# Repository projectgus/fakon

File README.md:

# Fakon

Fakon is open source hardware and software to present a Fake Hyundai Kona (*groan*) to transplanted powertrain modules taken from a real Hyundai Kona.

For more information, see [this blog post](https://projectgus.com/2024/12/fakon/).

## Disclaimers

Fakon is in early stage development, pre-alpha quality. Electric Vehicle modification involves serious risks, and there are zero guarantees about Fakon's quality, safety, or suitability for any purpose.

Fakon is developed exclusively through black-box reverse engineering techniques, and as such is prone to errors made in the reverse engineering process.

No content in Fakon is a derived work of any Copyrighted material owned by the Hyundai Kia Motor Company (HKMC) or their OEM suppliers.

## Licenses

* Software is licensed under the Mozilla Public License 2.0
* Hardware is licensed under the TAPR Open Hardware License 1.0

See LICENSE files for more details.

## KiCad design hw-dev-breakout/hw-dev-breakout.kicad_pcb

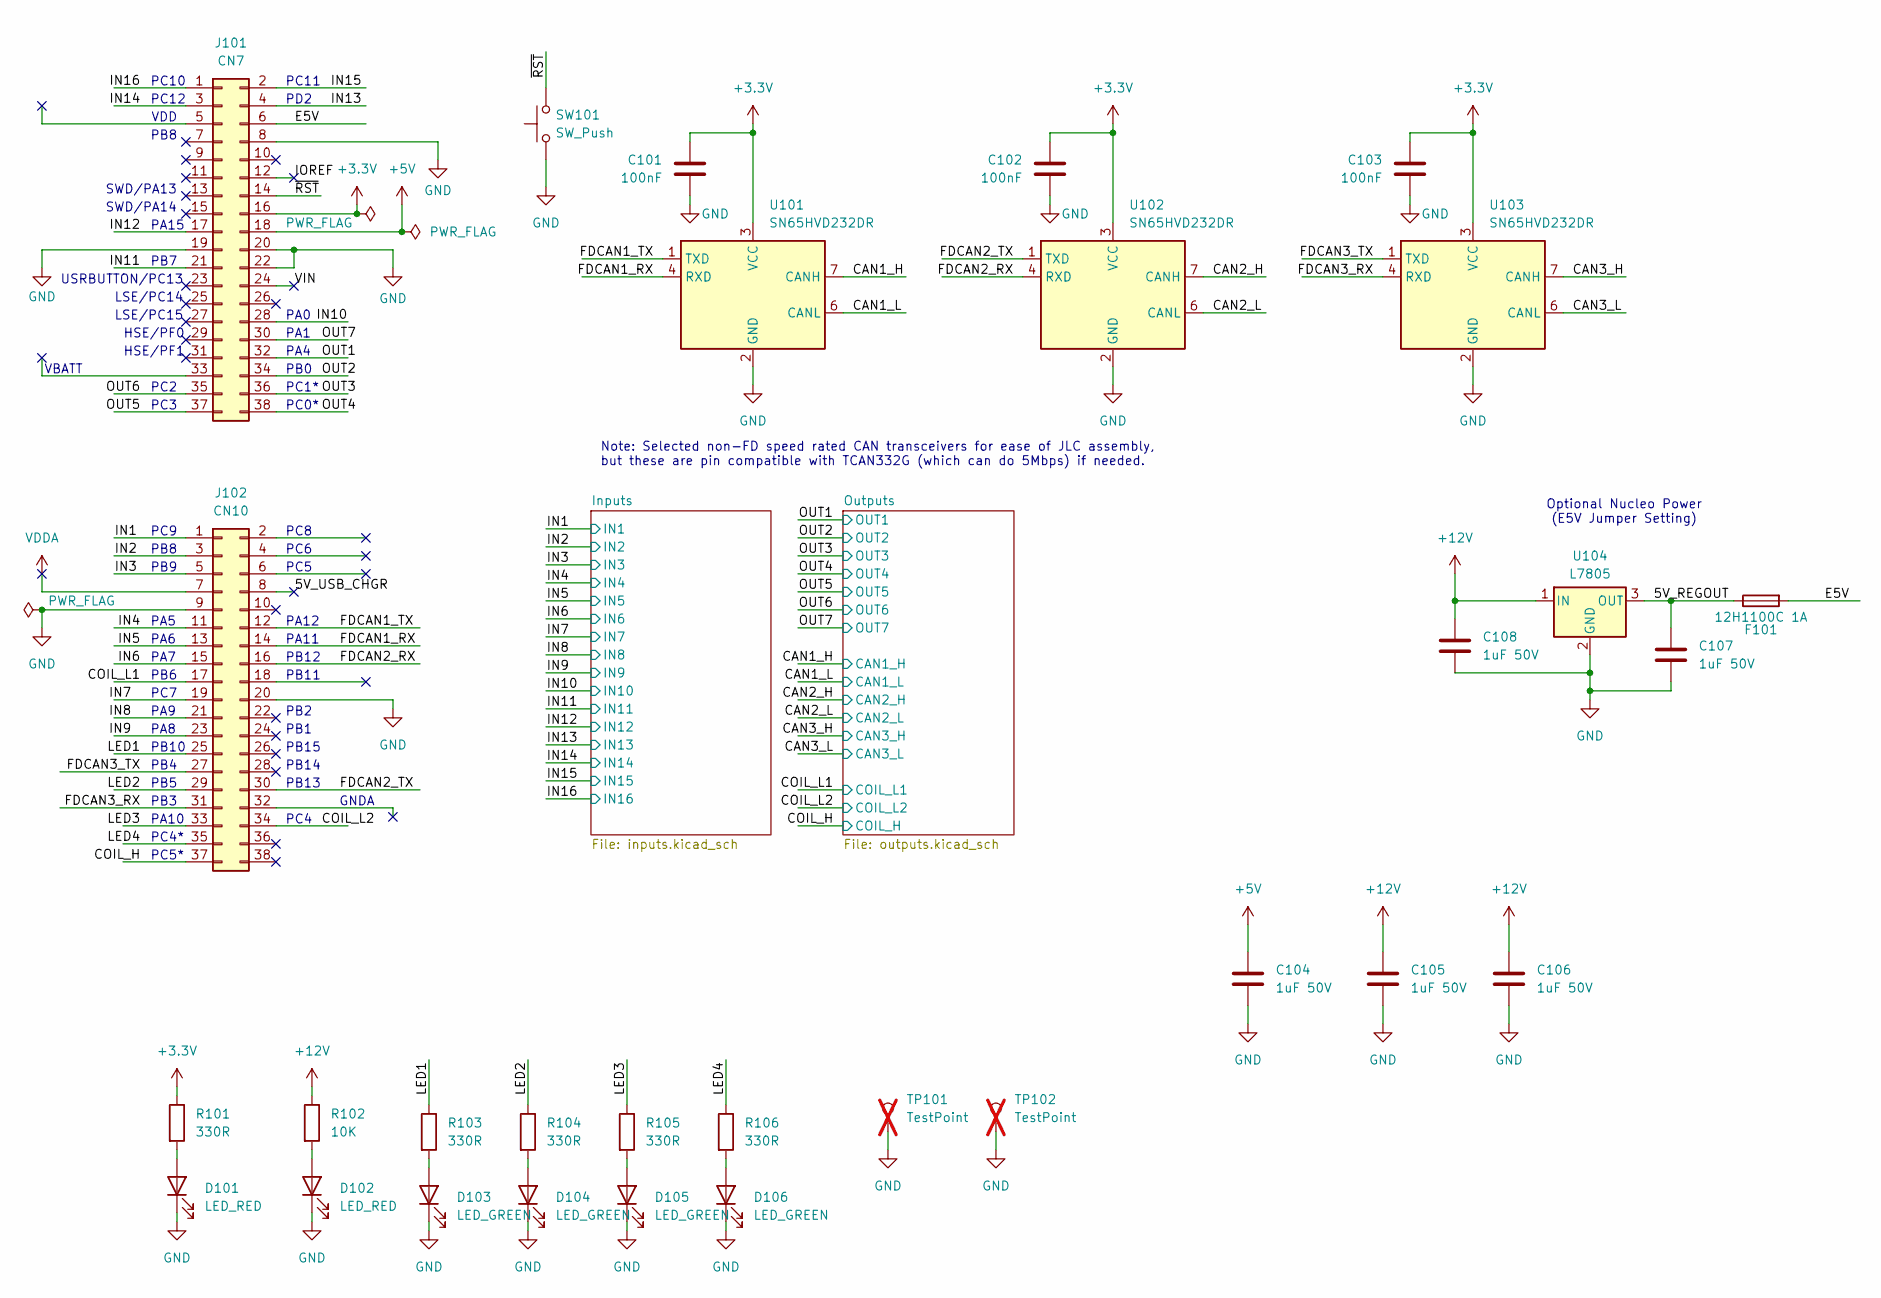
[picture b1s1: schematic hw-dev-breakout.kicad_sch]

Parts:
C101, C102, C103: 100nF; C_0603_1608Metric; LCSC Part # C14663
C104, C105, C106, C107, C108: 1uF 50V; C_1206_3216Metric; LCSC Part # C1848
D101, D102: LED_RED; LED_0603_1608Metric; LCSC Part # C2286
D103, D104, D105, D106: LED_GREEN; LED_0805_2012Metric; LCSC Part # C2297
F101: 12H1100C 1A; Fuse_1206_3216Metric; LCSC Part # C182308
J101: CN7; PinSocket_2x19_P2.54mm_Vertical; LCSC Part # C18905898
J102: CN10; PinSocket_2x19_P2.54mm_Vertical; LCSC Part # C18905898
R101, R103, R104, R105, R106: 330R; R_0603_1608Metric; LCSC Part # C23138
R102: 10K; R_0603_1608Metric; LCSC Part # C25804
SW101: SW_Push; SW_PUSH_6mm_H8mm; LCSC Part # C2889015
TP101, TP102: TestPoint; TestPoint_Pad_4.0x4.0mm; not fitted
U101, U102, U103: SN65HVD232DR; SOIC-8_3.9x4.9mm_P1.27mm; LCSC Part # C30530
U104: L7805; TO-252-2; LCSC Part # C58069

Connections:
+3.3V: C101.1, C102.1, C103.1, J101.16, R101.1, U101.3 (VCC), U102.3 (VCC), U103.3 (VCC); also elsewhere on the board
+5V: C104.1, J101.18; also elsewhere on the board
+12V: C105.1, C106.1, C108.1, R102.1, U104.1 (IN); also elsewhere on the board
/5V_REGOUT: C107.1, F101.1, U104.3 (OUT)
/5V_USB_CHGR: J102.8
/CAN1_H: U101.7 (CANH); also elsewhere on the board
/CAN1_L: U101.6 (CANL); also elsewhere on the board
/CAN2_H: U102.7 (CANH); also elsewhere on the board
/CAN2_L: U102.6 (CANL); also elsewhere on the board
/CAN3_H: U103.7 (CANH); also elsewhere on the board
/CAN3_L: U103.6 (CANL); also elsewhere on the board
/COIL_H: J102.37; also elsewhere on the board
/COIL_L1: J102.17; also elsewhere on the board
/COIL_L2: J102.34; also elsewhere on the board
/E5V: F101.2, J101.6
/FDCAN1_RX: J102.14, U101.4 (RXD)
/FDCAN1_TX: J102.12, U101.1 (TXD)
/FDCAN2_RX: J102.16, U102.4 (RXD)
/FDCAN2_TX: J102.30, U102.1 (TXD)
/FDCAN3_RX: J102.31, U103.4 (RXD)
/FDCAN3_TX: J102.27, U103.1 (TXD)
/IN1: J102.1; also elsewhere on the board
/IN2: J102.3; also elsewhere on the board
/IN3: J102.5; also elsewhere on the board
/IN4: J102.11; also elsewhere on the board
/IN5: J102.13; also elsewhere on the board
/IN6: J102.15; also elsewhere on the board
/IN7: J102.19; also elsewhere on the board
/IN8: J102.21; also elsewhere on the board
/IN9: J102.23; also elsewhere on the board
/IN10: J101.28; also elsewhere on the board
/IN11: J101.21; also elsewhere on the board
/IN12: J101.17; also elsewhere on the board
/IN13: J101.4; also elsewhere on the board
/IN14: J101.3; also elsewhere on the board
/IN15: J101.2; also elsewhere on the board
/IN16: J101.1; also elsewhere on the board
/IOREF: J101.12
/LED1: J102.25, R103.1
/LED2: J102.29, R104.1
/LED3: J102.33, R105.1
/LED4: J102.35, R106.1
/OUT1: J101.32; also elsewhere on the board
/OUT2: J101.34; also elsewhere on the board
/OUT3: J101.36; also elsewhere on the board
/OUT4: J101.38; also elsewhere on the board
/OUT5: J101.37; also elsewhere on the board
/OUT6: J101.35; also elsewhere on the board
/OUT7: J101.30; also elsewhere on the board
/VIN: J101.24
/~RST: J101.14, SW101.2
GND: C101.2, C102.2, C103.2, C104.2, C105.2, C106.2, C107.2, C108.2, D101.1 (K), D102.1 (K), D103.1 (K), D104.1 (K), D105.1 (K), D106.1 (K), J101.8, J101.19, J101.20, J101.22, J102.9, J102.20, SW101.1, TP101.1, TP102.1, U101.2 (GND), U102.2 (GND), U103.2 (GND), U104.2 (GND); also elsewhere on the board
unnamed: D101.2 (A), R101.2
unnamed: D102.2 (A), R102.2
unnamed: D103.2 (A), R103.2
unnamed: D104.2 (A), R104.2
unnamed: D105.2 (A), R105.2
unnamed: D106.2 (A), R106.2
VDDA: J102.7

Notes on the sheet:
PD2
PB8
PA0
SWD/PA13
VDD
PB11
PC5*
PC8
PA8
PB9
PA9
PC0*
PA15
Note: Selected non-FD speed rated CAN transceivers for ease of JLC assembly, but these are pin compatible with TCAN332G (which can do 5Mbps) if needed.
PC4*
PB4
PC7
PC12
LSE/PC14
VBATT
Optional Nucleo Power (E5V Jumper Setting)
PB5
PB3
PB7
PC3
USRBUTTON/PC13
PC10
PA7
PB15
PA5
PB6
PC5
PB10
HSE/PF0
PA10
PC11
PA1
PB12
PC9
HSE/PF1

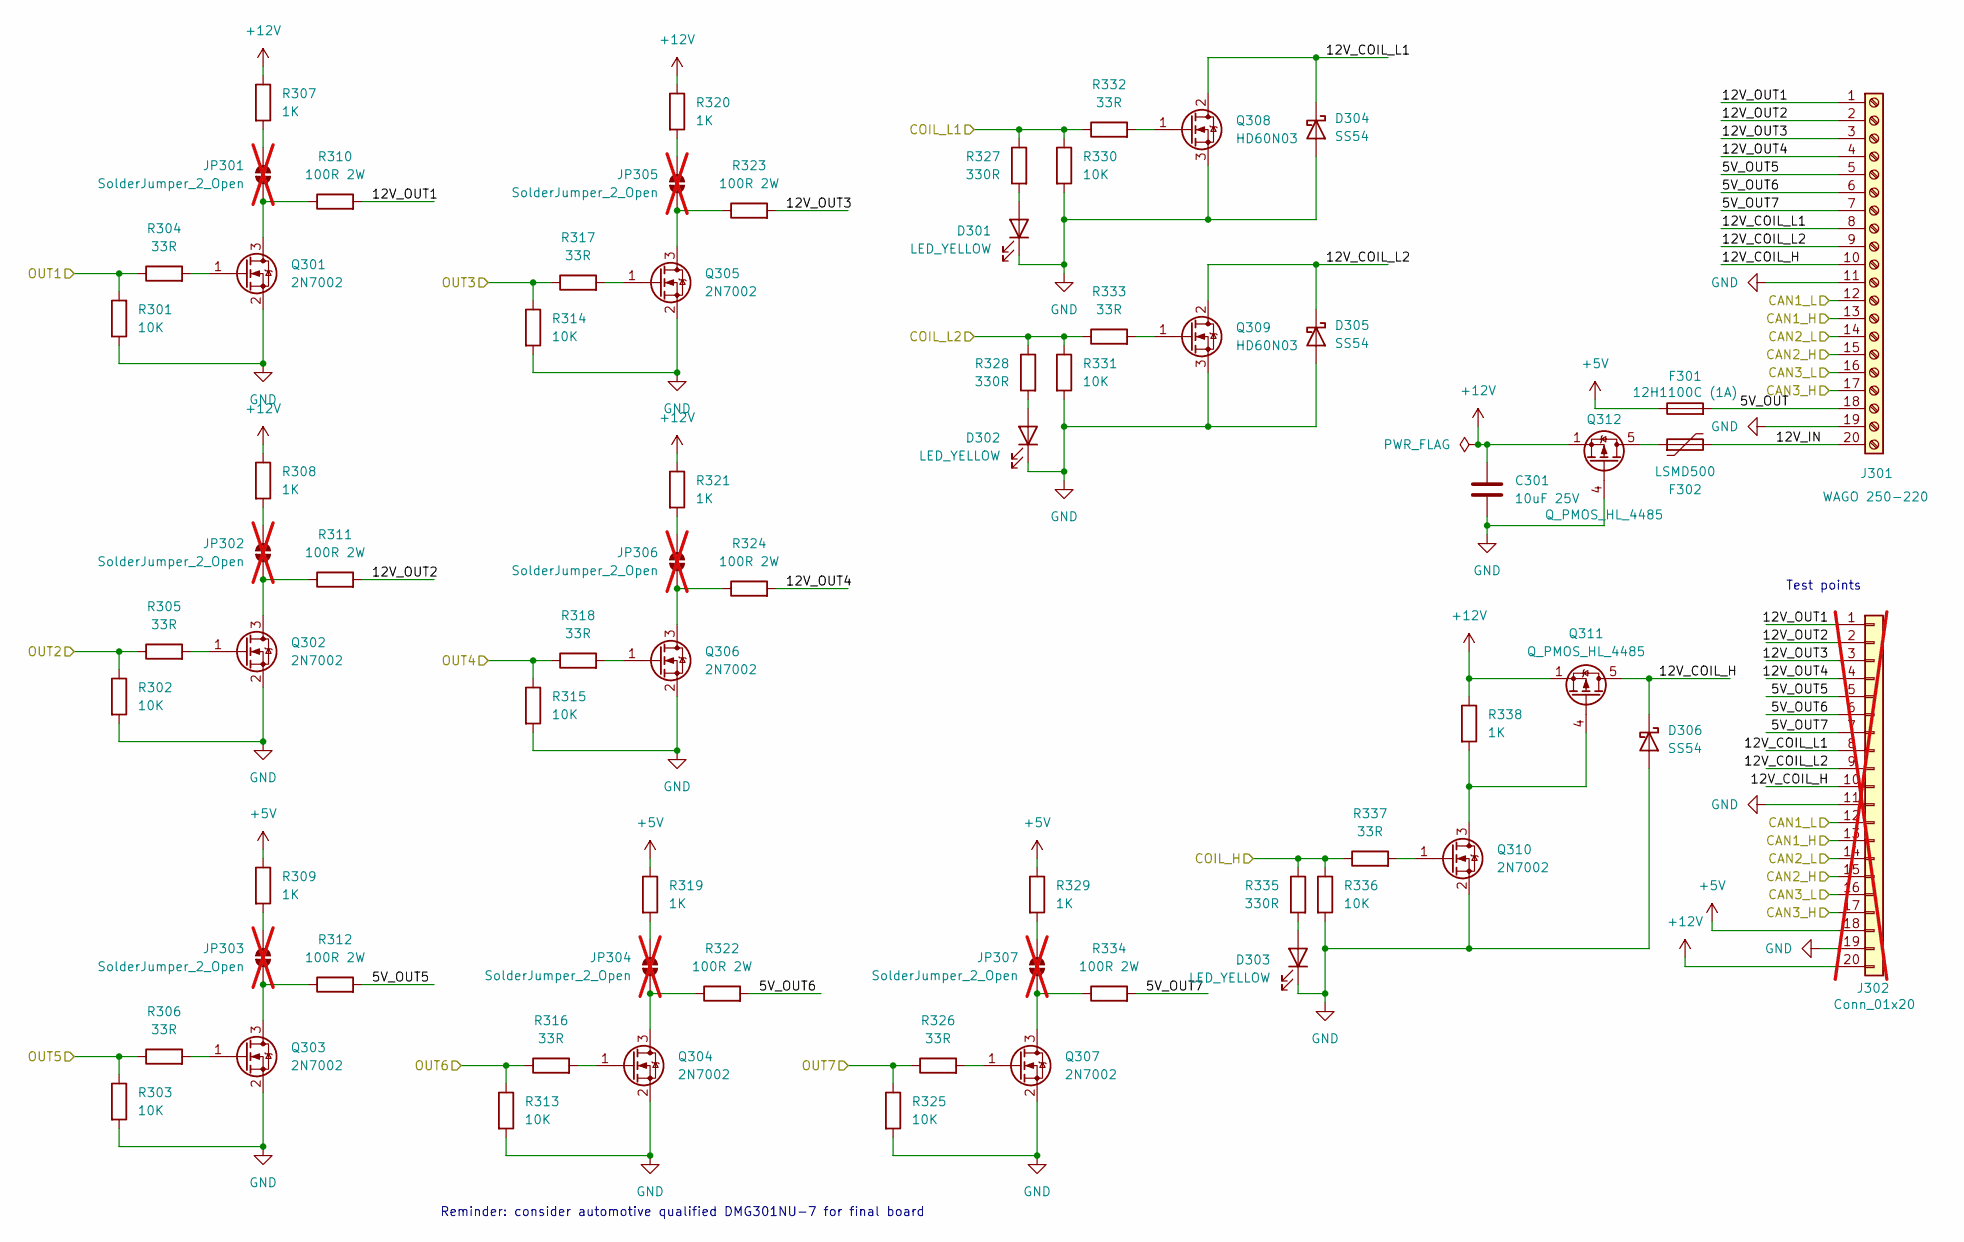
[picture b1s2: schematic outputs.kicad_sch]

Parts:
C301: 10uF 25V; CP_Elec_4x4.5; LCSC Part # C4747969
D301, D302, D303: LED_YELLOW; LED_0603_1608Metric; LCSC Part # C72038
D304, D305, D306: SS54; D_SMA; LCSC Part # C22452
F301: 12H1100C (1A); Fuse_1206_3216Metric; LCSC Part # C182308
F302: LSMD500; Fuse_2920_7451Metric; LCSC Part # C262045
J301: WAGO 250-220; WAGO 250-22; LCSC Part # C2833599
J302: Conn_01x20; PinSocket_1x20_P2.54mm_Vertical; not fitted
JP301, JP302, JP303, JP304, JP305, JP306, JP307: SolderJumper_2_Open; SolderJumper-2_P1.3mm_Open_Pad1.0x1.5mm; not fitted
Q301, Q302, Q303, Q304, Q305, Q306, Q307, Q310: 2N7002; SOT-23; LCSC Part # C8545
Q308, Q309: HD60N03; TO-252-2; LCSC Part # C216259
Q311, Q312: Q_PMOS_HL_4485; SOP-8_3.9x4.9mm_P1.27mm; LCSC Part # C7499854
R301, R302, R303, R313, R314, R315, R325, R330, R331, R336: 10K; R_0603_1608Metric; LCSC Part # C25804
R304, R305, R306, R316, R317, R318, R326, R332, R333, R337: 33R; R_0603_1608Metric; LCSC Part # C23140
R307, R308, R309, R319, R320, R321, R329, R338: 1K; R_0603_1608Metric; LCSC Part # C21190
R310, R311, R312, R322, R323, R324, R334: 100R 2W; R_2512_6332Metric; LCSC Part # C175280
R327, R328, R335: 330R; R_0603_1608Metric; LCSC Part # C23138

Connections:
+5V: F301.1, J302.18, R309.1, R319.1, R329.1; also elsewhere on the board
+12V: C301.1, J302.20, Q311.1 (S), Q311.2 (S), Q311.3 (S), Q312.1 (S), Q312.2 (S), Q312.3 (S), R307.1, R308.1, R320.1, R321.1, R338.1; also elsewhere on the board
/CAN1_H: J301.13, J302.13; also elsewhere on the board
/CAN1_L: J301.12, J302.12; also elsewhere on the board
/CAN2_H: J301.15, J302.15; also elsewhere on the board
/CAN2_L: J301.14, J302.14; also elsewhere on the board
/CAN3_H: J301.17, J302.17; also elsewhere on the board
/CAN3_L: J301.16, J302.16; also elsewhere on the board
/COIL_H: R335.1, R336.1, R337.1; also elsewhere on the board
/COIL_L1: R327.1, R330.1, R332.1; also elsewhere on the board
/COIL_L2: R328.1, R331.1, R333.1; also elsewhere on the board
/OUT1: R301.2, R304.1; also elsewhere on the board
/OUT2: R302.1, R305.1; also elsewhere on the board
/OUT3: R314.1, R317.1; also elsewhere on the board
/OUT4: R315.1, R318.1; also elsewhere on the board
/OUT5: R303.1, R306.1; also elsewhere on the board
/OUT6: R313.1, R316.1; also elsewhere on the board
/OUT7: R325.1, R326.1; also elsewhere on the board
/Outputs/5V_OUT: F301.2, J301.18
/Outputs/5V_OUT5: J301.5, J302.5, R312.2
/Outputs/5V_OUT6: J301.6, J302.6, R322.2
/Outputs/5V_OUT7: J301.7, J302.7, R334.2
/Outputs/12V_COIL_H: D306.1 (K), J301.10, J302.10, Q311.5 (D), Q311.6 (D), Q311.7 (D), Q311.8 (D)
/Outputs/12V_COIL_L1: D304.1 (K), J301.8, J302.8, Q308.2 (D)
/Outputs/12V_COIL_L2: D305.1 (K), J301.9, J302.9, Q309.2 (D)
/Outputs/12V_IN: F302.2, J301.20
/Outputs/12V_OUT1: J301.1, J302.1, R310.2
/Outputs/12V_OUT2: J301.2, J302.2, R311.2
/Outputs/12V_OUT3: J301.3, J302.3, R323.2
/Outputs/12V_OUT4: J301.4, J302.4, R324.2
GND: C301.2, D301.1 (K), D302.1 (K), D303.1 (K), D304.2 (A), D305.2 (A), D306.2 (A), J301.11, J301.19, J302.11, J302.19, Q301.2 (S), Q302.2 (S), Q303.2 (S), Q304.2 (S), Q305.2 (S), Q306.2 (S), Q307.2 (S), Q308.3 (S), Q309.3 (S), Q310.2 (S), Q312.4 (G), R301.1, R302.2, R303.2, R313.2, R314.2, R315.2, R325.2, R330.2, R331.2, R336.2; also elsewhere on the board
unnamed: D301.2 (A), R327.2
unnamed: D302.2 (A), R328.2
unnamed: D303.2 (A), R335.2
unnamed: F302.1, Q312.5 (D), Q312.6 (D), Q312.7 (D), Q312.8 (D)
unnamed: JP301.1 (A), R307.2
unnamed: JP301.2 (B), Q301.3 (D), R310.1
unnamed: JP302.1 (A), R308.2
unnamed: JP302.2 (B), Q302.3 (D), R311.1
unnamed: JP303.1 (A), R309.2
unnamed: JP303.2 (B), Q303.3 (D), R312.1
unnamed: JP304.1 (A), R319.2
unnamed: JP304.2 (B), Q304.3 (D), R322.1
unnamed: JP305.1 (A), R320.2
unnamed: JP305.2 (B), Q305.3 (D), R323.1
unnamed: JP306.1 (A), R321.2
unnamed: JP306.2 (B), Q306.3 (D), R324.1
unnamed: JP307.1 (A), R329.2
unnamed: JP307.2 (B), Q307.3 (D), R334.1
unnamed: Q301.1 (G), R304.2
unnamed: Q302.1 (G), R305.2
unnamed: Q303.1 (G), R306.2
unnamed: Q304.1 (G), R316.2
unnamed: Q305.1 (G), R317.2
unnamed: Q306.1 (G), R318.2
unnamed: Q307.1 (G), R326.2
unnamed: Q308.1 (G), R332.2
unnamed: Q309.1 (G), R333.2
unnamed: Q310.3 (D), Q311.4 (G), R338.2
unnamed: Q310.1 (G), R337.2

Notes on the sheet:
Reminder: consider automotive qualified DMG301NU-7 for final board
Test points

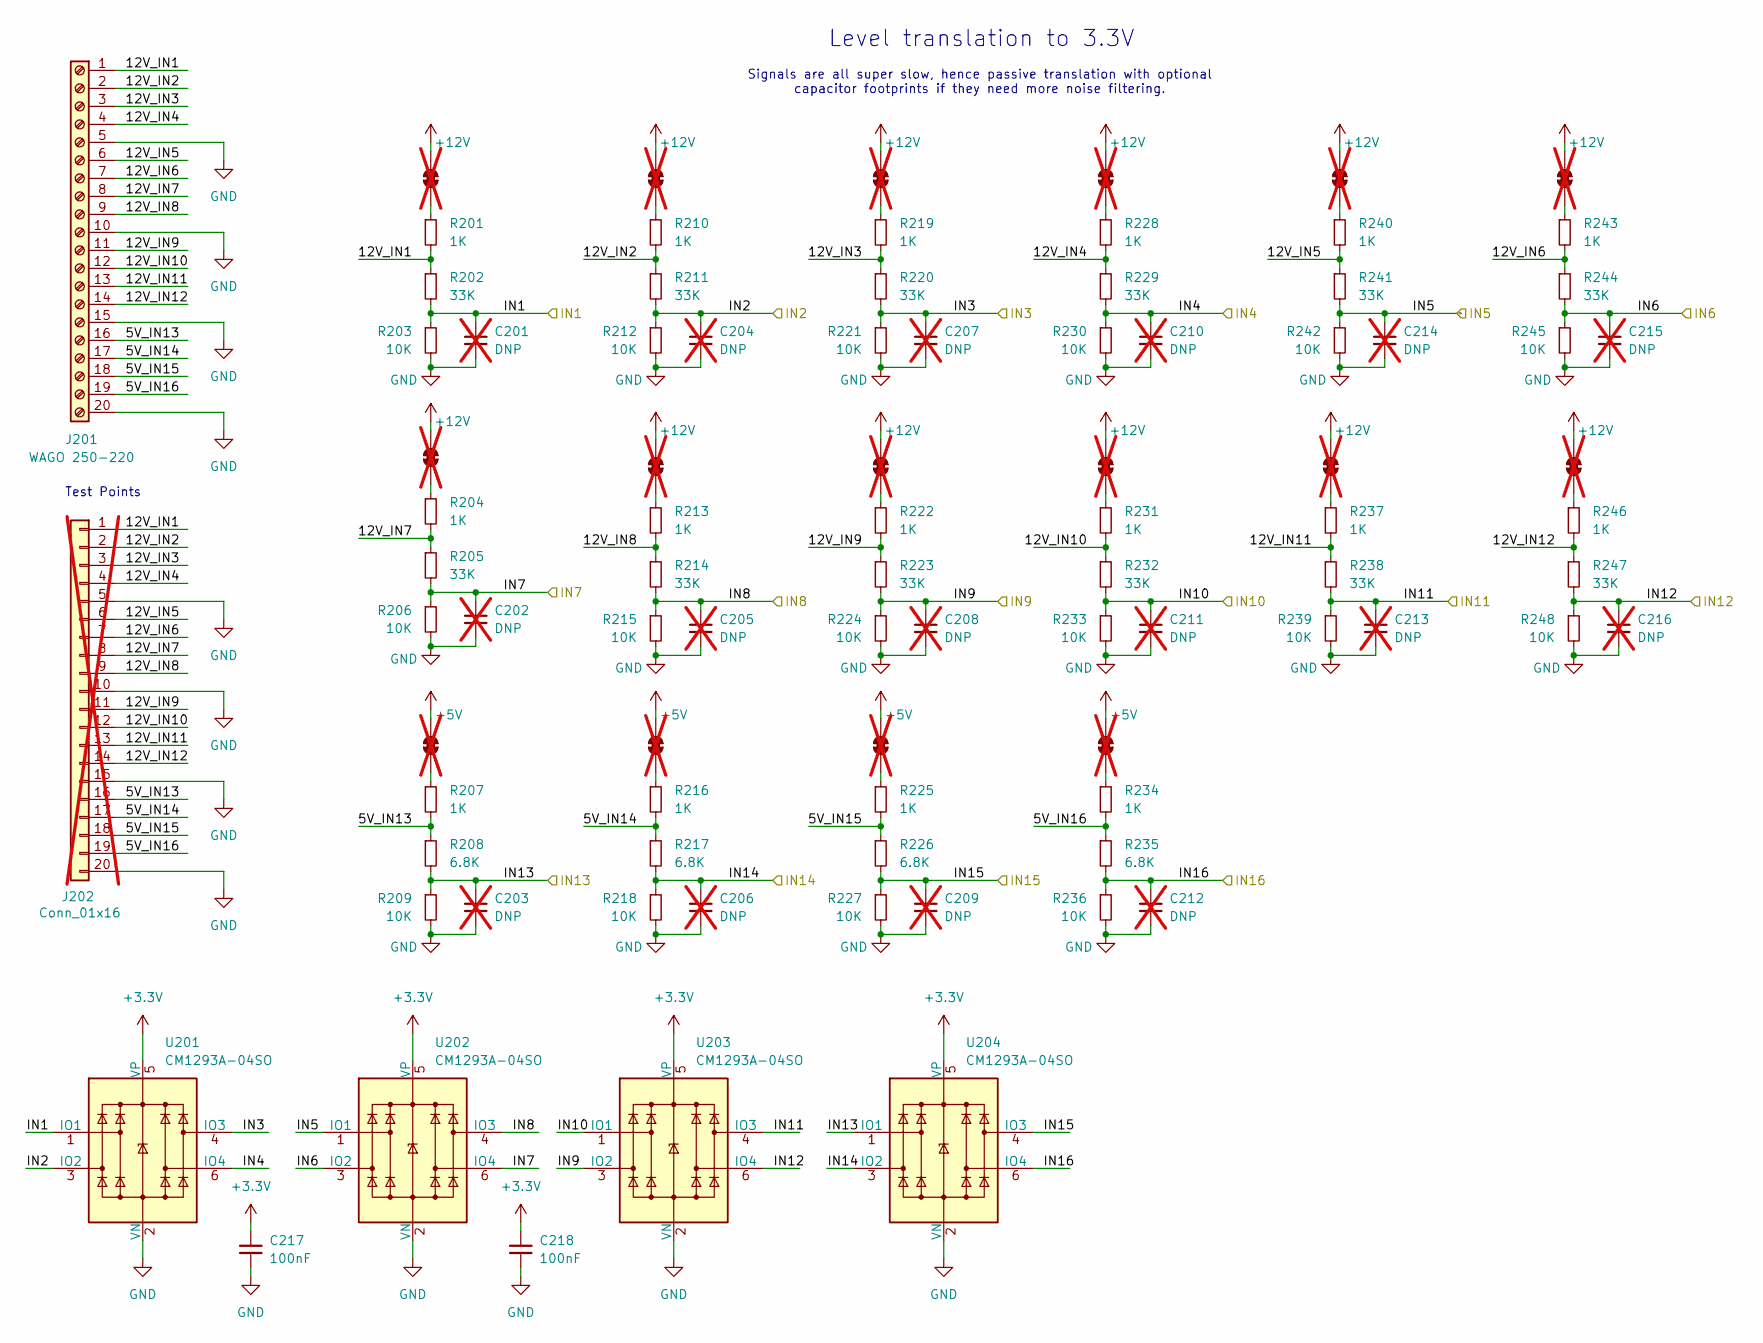
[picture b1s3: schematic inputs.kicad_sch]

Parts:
C201, C202, C203, C204, C205, C206, C207, C208, C209, C210, C211, C212, C213, C214, C215, C216: DNP; C_0603_1608Metric; not fitted
C217, C218: 100nF; C_0603_1608Metric; LCSC Part # C14663
J201: WAGO 250-220; WAGO 250-22; LCSC Part # C2833599
J202: Conn_01x16; PinSocket_1x20_P2.54mm_Vertical; not fitted
JP201, JP202, JP203, JP204, JP205, JP206, JP207, JP208, JP209, JP210, JP211, JP212, JP213, JP214, JP215, JP216: SolderJumper_2_Bridged; SolderJumper-2_P1.3mm_Bridged_Pad1.0x1.5mm; not fitted
R201, R204, R207, R210, R213, R216, R219, R222, R225, R228, R231, R234, R237, R240, R243, R246: 1K; R_0603_1608Metric; LCSC Part # C21190
R202, R205, R211, R214, R220, R223, R229, R232, R238, R241, R244, R247: 33K; R_0603_1608Metric; LCSC Part # C4216
R203, R206, R209, R212, R215, R218, R221, R224, R227, R230, R233, R236, R239, R242, R245, R248: 10K; R_0603_1608Metric; LCSC Part # C25804
R208, R217, R226, R235: 6.8K; R_0603_1608Metric; LCSC Part # C23212
U201, U202, U203, U204: CM1293A-04SO; SOT-23-6; LCSC Part # C393377

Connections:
+3.3V: C217.1, C218.1, U201.5 (VP), U202.5 (VP), U203.5 (VP), U204.5 (VP); also elsewhere on the board
+5V: JP203.2 (B), JP206.2 (B), JP209.2 (B), JP212.2 (B); also elsewhere on the board
+12V: JP201.2 (B), JP202.2 (B), JP204.2 (B), JP205.2 (B), JP207.2 (B), JP208.2 (B), JP210.2 (B), JP211.2 (B), JP213.2 (B), JP214.2 (B), JP215.2 (B), JP216.2 (B); also elsewhere on the board
/IN1: C201.1, R202.2, R203.1, U201.1 (IO1); also elsewhere on the board
/IN2: C204.1, R211.2, R212.1, U201.3 (IO2); also elsewhere on the board
/IN3: C207.1, R220.2, R221.1, U201.4 (IO3); also elsewhere on the board
/IN4: C210.1, R229.2, R230.1, U201.6 (IO4); also elsewhere on the board
/IN5: C214.1, R241.2, R242.1, U202.1 (IO1); also elsewhere on the board
/IN6: C215.1, R244.2, R245.1, U202.3 (IO2); also elsewhere on the board
/IN7: C202.1, R205.2, R206.1, U202.6 (IO4); also elsewhere on the board
/IN8: C205.1, R214.2, R215.1, U202.4 (IO3); also elsewhere on the board
/IN9: C208.1, R223.2, R224.1, U203.3 (IO2); also elsewhere on the board
/IN10: C211.1, R232.2, R233.1, U203.1 (IO1); also elsewhere on the board
/IN11: C213.1, R238.2, R239.1, U203.4 (IO3); also elsewhere on the board
/IN12: C216.1, R247.2, R248.1, U203.6 (IO4); also elsewhere on the board
/IN13: C203.1, R208.2, R209.1, U204.1 (IO1); also elsewhere on the board
/IN14: C206.1, R217.2, R218.1, U204.3 (IO2); also elsewhere on the board
/IN15: C209.1, R226.2, R227.1, U204.4 (IO3); also elsewhere on the board
/IN16: C212.1, R235.2, R236.1, U204.6 (IO4); also elsewhere on the board
/Inputs/5V_IN13: J201.16, J202.16, R207.2, R208.1
/Inputs/5V_IN14: J201.17, J202.17, R216.2, R217.1
/Inputs/5V_IN15: J201.18, J202.18, R225.2, R226.1
/Inputs/5V_IN16: J201.19, J202.19, R234.2, R235.1
/Inputs/12V_IN1: J201.1, J202.1, R201.2, R202.1
/Inputs/12V_IN2: J201.2, J202.2, R210.2, R211.1
/Inputs/12V_IN3: J201.3, J202.3, R219.2, R220.1
/Inputs/12V_IN4: J201.4, J202.4, R228.2, R229.1
/Inputs/12V_IN5: J201.6, J202.6, R240.2, R241.1
/Inputs/12V_IN6: J201.7, J202.7, R243.2, R244.1
/Inputs/12V_IN7: J201.8, J202.8, R204.2, R205.1
/Inputs/12V_IN8: J201.9, J202.9, R213.2, R214.1
/Inputs/12V_IN9: J201.11, J202.11, R222.2, R223.1
/Inputs/12V_IN10: J201.12, J202.12, R231.2, R232.1
/Inputs/12V_IN11: J201.13, J202.13, R237.2, R238.1
/Inputs/12V_IN12: J201.14, J202.14, R246.2, R247.1
GND: C201.2, C202.2, C203.2, C204.2, C205.2, C206.2, C207.2, C208.2, C209.2, C210.2, C211.2, C212.2, C213.2, C214.2, C215.2, C216.2, C217.2, C218.2, J201.5, J201.10, J201.15, J201.20, J202.5, J202.10, J202.15, J202.20, R203.2, R206.2, R209.2, R212.2, R215.2, R218.2, R221.2, R224.2, R227.2, R230.2, R233.2, R236.2, R239.2, R242.2, R245.2, R248.2, U201.2 (VN), U202.2 (VN), U203.2 (VN), U204.2 (VN); also elsewhere on the board
unnamed: JP201.1 (A), R201.1
unnamed: JP202.1 (A), R204.1
unnamed: JP203.1 (A), R207.1
unnamed: JP204.1 (A), R210.1
unnamed: JP205.1 (A), R213.1
unnamed: JP206.1 (A), R216.1
unnamed: JP207.1 (A), R219.1
unnamed: JP208.1 (A), R222.1
unnamed: JP209.1 (A), R225.1
unnamed: JP210.1 (A), R228.1
unnamed: JP211.1 (A), R231.1
unnamed: JP212.1 (A), R234.1
unnamed: JP213.1 (A), R237.1
unnamed: JP214.1 (A), R240.1
unnamed: JP215.1 (A), R243.1
unnamed: JP216.1 (A), R246.1

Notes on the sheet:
Level translation to 3.3V
Signals are all super slow, hence passive translation with optional capacitor footprints if they need more noise filtering.
Test Points

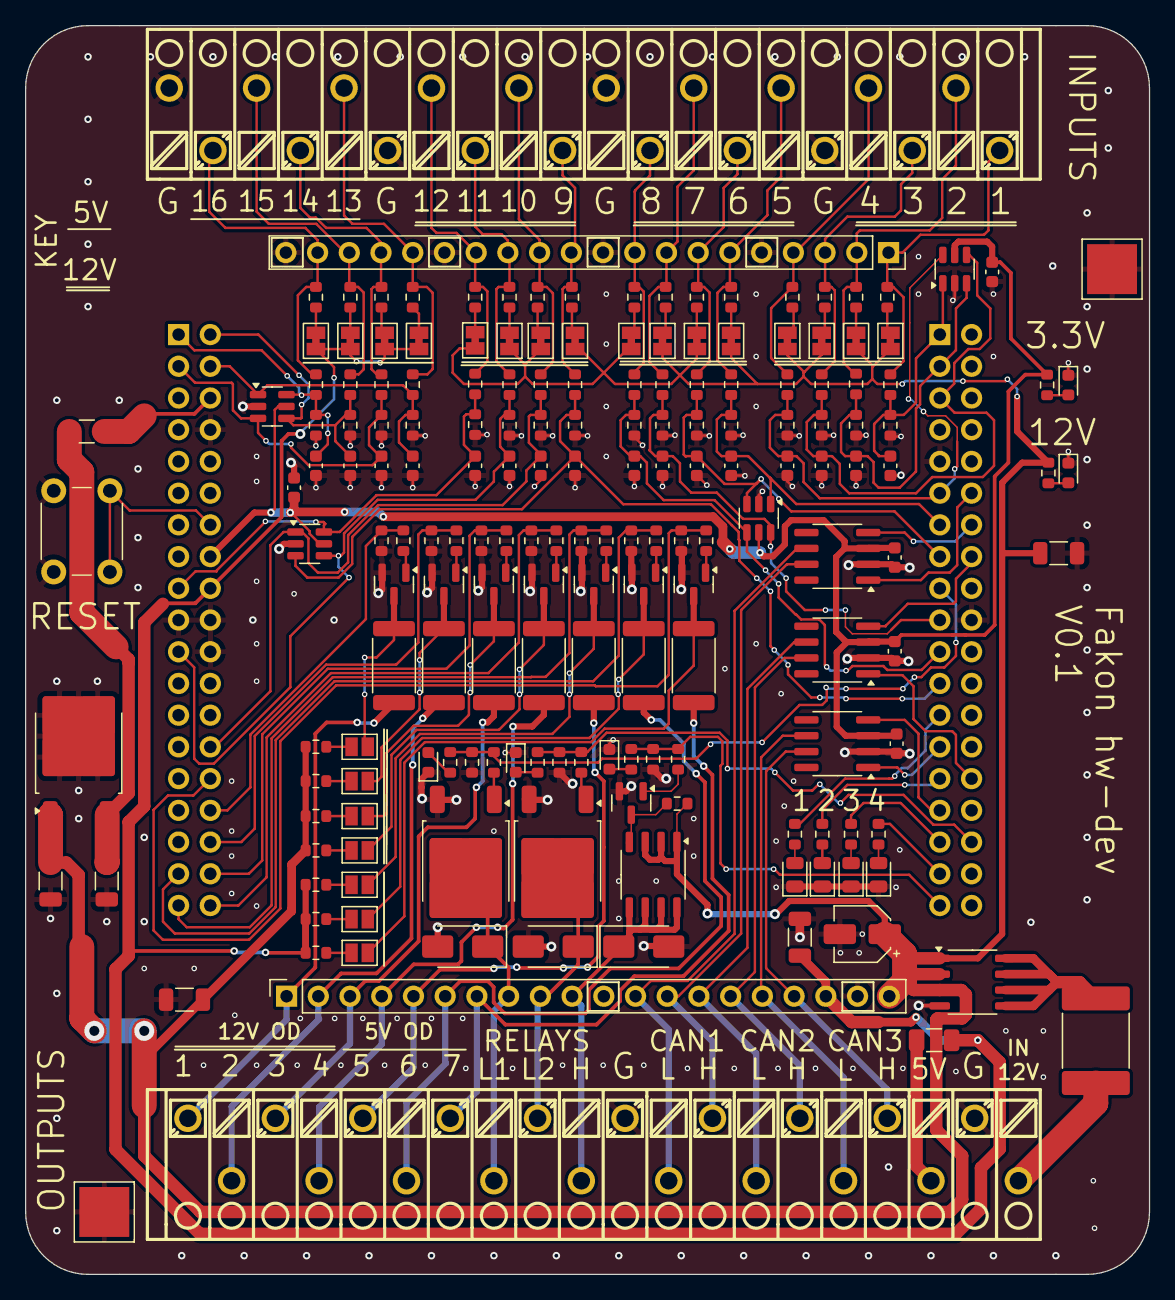
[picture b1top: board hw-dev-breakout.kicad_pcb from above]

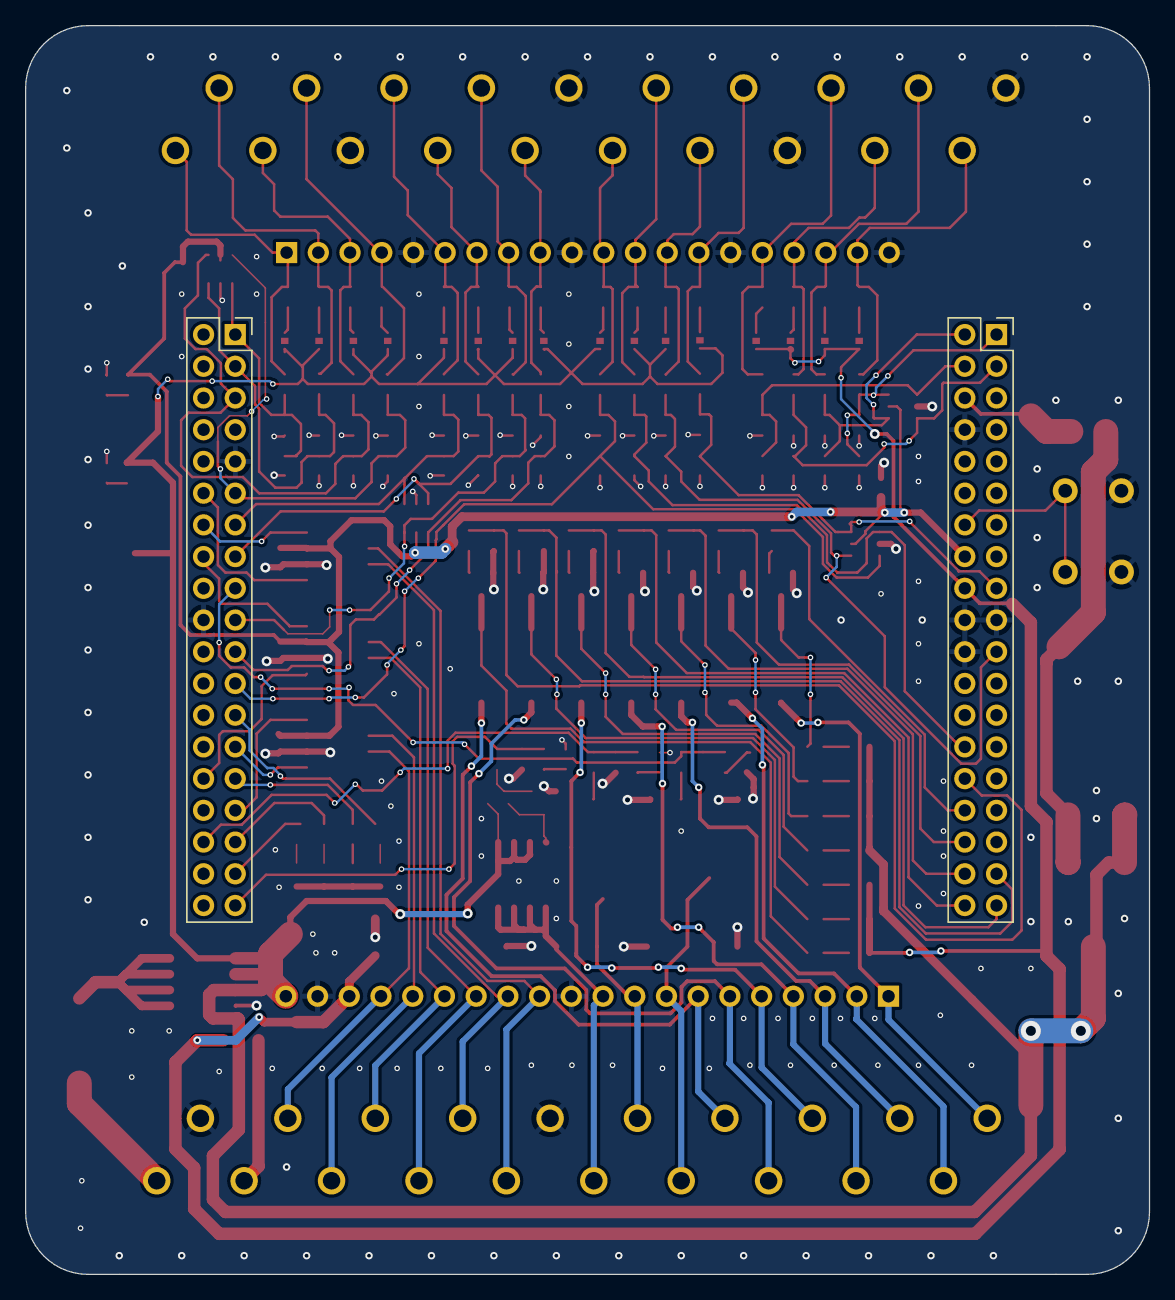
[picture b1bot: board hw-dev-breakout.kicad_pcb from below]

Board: 2 copper layers, 90.0 x 100.0 mm, 186 parts (2 on the bottom side), 128 nets.

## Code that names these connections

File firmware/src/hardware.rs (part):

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    let _pin_in16 = gpioc.pc10; // 5V

    // Signal outputs
    let pin_out1 = gpioa.pa4; // 12V, TIM3_CH2
    let pin_out2 = gpiob.pb0; // 12V, TIM3_CH3
    let _pin_out3 = gpioc.pc1; // 12V, TIM1_CH2
    let _pin_out4 = gpioc.pc0; // 12V, TIM1_CH1
    let pin_out5 = gpioc.pc3; // 5V, TIM1_CH4
    let _pin_out6 = gpioc.pc2; // 5V, TIM1_CH3
    let _pin_out7 = gpioa.pa1; // 5V, TIM2_CH2 or TIM5_CH2

    // Relay coil drivers
    let pin_coil_l1 = gpiob.pb6;
    let _pin_coil_l2 = gpioc.pc4; // also LED4, oops
    let pin_coil_h = gpioc.pc5;

    // LEDs, all green, all active high
    let led1 = gpiob.pb10.into_push_pull_output();
    let _led2 = gpiob.pb5.into_push_pull_output();
    let mut led3 = gpioa.pa10.into_push_pull_output();
    // led4 accidentally shared with pin_coil_l2

    // Use LED3 as a "firmware not asleep" status light
    led3.set_high().unwrap();
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
    // OUT5 => SCU Park TX (5V 10Hz soft PWM)
    // (inverted due to drive FET)
    let scu_park_tx = InvertedPin::new(pin_out5.into_push_pull_output());

    // IN13 => SCU Park RX (5V 10Hz PWM via interrupt)
    let mut scu_park_rx = pin_in13.into_floating_input();
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
    // OUT1 => SRS Crash signal, 50Hz soft PWM
    // Inverted as MCU pin drives a FET gate for open drain output
    let srs_crash_out = InvertedPin::new(pin_out1.into_push_pull_output());

    // IN1 => IG1 ignition on input
    let ig1_on_input = pin_in1.into_floating_input();
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    let ev_ready = InvertedPin::new(pin_in3.into_floating_input());

    // RELAY L1 - IG3 relay coil enable
    let relay_ig3 = pin_coil_l1.into_push_pull_output();

    // LED 1 - Ignition Status
    let led_ignition = led1.into_push_pull_output();

    // OUT2 => Charge Lock Direction output
    // Inverted as MCU drives FET gate
    let charge_lock_dir = InvertedPin::new(pin_out2.into_push_pull_output());

    // Hardware design flaw: I planned to use high and low relay coil drivers for
    // the charge port but misunderstood the drive design. Still using high side driver
    // here, it's overkill but has the property of being low on reset!
    let charge_lock_drive = pin_coil_h.into_push_pull_output();

    // IN15 => Charge Port Lock input, no pullup, 5K Pulldown.
    let charge_lock_sensor = pin_in15.into_floating_input();
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
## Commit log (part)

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2024-07-20 hw-dev-breakout: Add list of connections
2024-07-20 hw-dev-breakout: Initial schematic, STM32 Nucleo-64 template with NUCLEO-G474RE pin names
2024-07-22 WIP: Active level shifting, too many components
2024-07-26 Schematic mostly done, pre-resistor pack swap
2024-08-02 Add footprint library with WAGO 250-220 footprint
    Exported from LCSC EasyEDA.
2024-08-02 Complete schematic with footprint assignments
2024-08-02 pcb: Move the Nucleo outline onto a comment layout
2024-08-03 pcb: Initial components placed
2024-08-03 pcb: Partially routed
2024-08-04 pcb: Routed, using jlc 4 layer specs
2024-08-05 pcb: Routed for 2 layer, fixed P-fet error
2024-08-05 Add reverse polarity protection for 12V In
2024-08-07 Final cleanups for initial fab run
2024-08-07 pcb: Fix the placement origin point
2024-08-12 firmware: Start from rtic-rs/defmt-app-template
    Commit b24c3f42da as-is.
2024-08-12 pcb: Update some LCSC part numbers
2024-08-12 firmware: Minimal app running on Nucleo-G4 board
2024-08-15 firmware: Minimal running on PLL @ 128MHz (untested)
2024-08-15 firmware: minimal: ext Nucleo HSE as main clock source
2024-08-16 firmware: Ported can_queue to use fdcan.
    Compiles, untested.
2024-08-16 firmware: Inching towards a hardware abstraction.
2024-08-16 firmware: Add systick timer, maybe?
2024-08-16 firmware: Abstract hardware to its own module.
2024-08-19 firmware: Abstract srscm to its own module, further cleanups.
2024-08-20 firmware: WIP: periodic CAN transmit, IEB support
2024-08-20 firmware: Add IGPM, structure starting to feel unwieldy.
2024-08-26 WIP: firmware: single task per module, make a very simple timer for each message period.
    This is smaller firmware-wise and I think easier to reason about. The
    implementation is very simple, I think could make a cleverer one but it seems
    fit for purpose like this...
2024-08-29 firmware: Add pcan interrupt handler, not very happy with this
2024-08-29 firmware: Big can_queue refactor, clean up some hairy bits
2024-08-29 firmware: Rename 'minimal' binary
2024-08-29 firmare: Read the ignition power input, refactor car state.
2024-09-01 firmware: Fix CAN timings
    Requires fix in stm32g4xx-hal as well.
2024-09-01 firmware: Fix defmt for queued CAN frames.
2024-09-05 firmware: Working CAN TX!
2024-09-05 firmware: Fix some can TX timings.
2024-09-05 firmware: CAN RX is working, tweak some formatting
2024-10-03 firmware: Add very rough IG3 relay control and ignition monitor.
    Will go into Ready now!
2024-10-03 can_queue: Remove enable_transmission_interrupts, decided not to implement.
2024-10-03 can_queue: Downgrade Error Passive from a panic to a warning.
    Not clear if fdcan driver has a way to recover from this state, though.
2024-10-04 fw: Model the SRS crash output as inverted.
    Means set_high() sets board output high (or floating as it's OD), set_low()
    drives it low.
    Via inverted-pin crate, an old version as stm32g4xx-hal uses
    embedded-hal 0.2 still.
2024-10-05 fw: Add DBC code generation, make available to firmware.
    Not used in firmware source, yet.
2024-10-05 fw: Use embedded_can traits with fdcan.
    Opens the door to passing dbc codegen structs direct to transmit().
2024-10-05 fw: Use dbc struct type for airbag TX, rename srscm to airbag_control.
    This struct has constant values so this is something of a no-op change,
    although it adds about 500 bytes of code size which is unfortunate.
2024-10-05 fw: Log received CAN packets (currently expensive)
2024-10-07 toolchain: Temporarily use a specific nightly
    Workaround for linking regression in linked issue.
2024-10-07 fw: Use defmt::Format trait for CAN messages
    About 1/3 of the code size overhead.
2024-10-07 fw: Remove manually copied FramePriority implementation.
2024-10-07 ieb: Use DBC structs for brake types.
    This adds about 4KB to the code size! and seems to have
    introduced the first reachable panic code path...
2024-10-11 fw: Refactor IGPM, IEB CAN messages to use DBC structs also.
    In the process started refining behaviours, which messages depend
    on ignition state, etc.
2024-10-11 fw: Start to model the ignition and contactor state more closely
2024-10-11 fw: Update some more fields based on log analysis
2024-10-12 fw: Skip diagnostic frame IDs for now
    Otherwise when a tester is connected it logs a lot of warnings/errors about
    being unable to parse the messages.
2024-10-12 fw: Small fixes from running on-vehicle
    - Promote some warnings to errors
    - Fix logging of the frame IDs (Debug2Format seems pretty inexpensive here)
    This version has run on the bench Kona, gone to Park & Neutral, same set of
    DTCs showing as pre-dbc_codegen refactors. (Except now also showing P0C17
    from the MCU but I think that's unrelated to anything we're doing.)
2024-10-13 fw: Alias the common Duration, Instant and Rate for more readable code.
2024-10-13 fw: Add a Fresh() wrapper type for values which can time out.
    Start by applying to the BMS CAN messages for the contactor and pre-charge
    states.
    This adds the concept of handling an unknown state if the relevant CAN
    message hasn't been received within the necessary time window.
2024-10-17 fw: Comment cleanup, formatting.
2024-10-17 fw: Add periodic logging of vehicle state
    Also wrap some other car parameters in Fresh.
2024-10-17 fw: Track and log the battery state of charge as well.
2024-10-17 fw: Remove toolchain version workaround
    nightly-2024-10-07 has fix for linked issue.
2024-10-18 fw: Confirmed working on bench.
    No change to previous DTCs.
2024-10-19 fw: Add CAN messages for stability control and steering status.
    Also a bunch of naming cleanups.
    No change in DTCs yet.
2024-10-20 fw: Use range pattern for counter field max.
    This shrinks the release firmware size by quite a bit as it removes a path to
    panic. It seems now the compiler can tell the range checks in set_counter() will
    always be met.
    (As the getters in dbc_codegen structs don't have any range bounds, there's no
    guarantee the old counter value wasn't out of range, which is odd as usually
    the field mask actually limits it as well...)
2024-10-20 fw: ieb: Set the Stability Control live counters properly.
2024-10-20 fw: ieb: Fix up the traction control message updates
    Also add a new trait to encapsulate updating counters and re-calculating
    checksums.
2024-10-20 fw: Add a convenience method for OutgoingMessage updates.
    As Frame isn't object-safe we still need a bit of copy and paste here, but
    hopefully less soon...
2024-10-21 fw: Add a periodic parking brake message.
2024-10-21 fw: Add some unknown messages
    Hopefully these can mostly be deleted later.
2024-10-21 fw: Optimise the CAN receive path.
    Was getting occasional CAN peripheral RX overrun flags (at least in Debug mode),
    have made the CAN IRQ the highest priority and also made it check more
    aggressively for receive interrupts now.
2024-10-21 fw: Update dbc, VCU no longer reports a DTC about brake unit comms!
    Still showing a DTC about losing communication with the gateway. :|
2024-10-26 fw: Actually send the Unknown messages.
    Unfortunately doesn't change the missing gateway DTC on the VCU.
2024-10-26 fw: Dump the error if DBC parsing fails.
    Goes from very terse (no details) to a full parse tree, but useful to find
    the place where it failed.
2024-10-28 fw: Add a bunch more unknown messages
2024-10-28 fw: Boost the TX queue depth.
    Necessary with all these new messages to avoid dropped messages.
2024-10-28 fw: Upgrade some warnings to errors so harder to miss.
    Especially with default log levels.
2024-10-28 fw: Always send charge settings message.
    Had this marked as IG3-on only, but it's actually always on.
2024-11-02 fw: Add missing UNK_588 message.
    No more DTC showing for gateway comms! :D
2024-11-02 fw: Add debouncing for power detection inputs
2024-11-02 fw: unknown: Remove messages not needed by VCU.
    VCU doesn't throw the U0146 Gateway message with these
    messages not present on bus.
2024-11-02 fw: igpm: Remove hu_datc_pe_00
    No DTCs seen after removing this message.
2024-11-02 fw: igpm: Move all remaining unknown messages to IGPM
    DBC update gives them new names indicating they're IGPM-related.
2024-11-02 fw: Add some top-level module comments
2024-11-06 fw: Remove From<&Frame> implementation from QueuedFrame.
    Doesn't seem necessary.
2024-11-07 fw: Swap back to stable toolchain, yay!
2024-11-07 fw: Refactor Repeater to not use select blocks
    Too many cancelled futures...
2024-11-07 fw: Log error if a repeater lags by a whole cycle
2024-11-07 fw: Minor doc comment cleanups
2024-11-07 WIP: Add SCU emulation.
    No tasks are currently spawned for SCU, as still unsure of what triggers the
    park actuator to lock/unlock.
2024-11-07 fw: Small cleanup
2024-11-07 fw: Refactor airbag_control and igpm to use PeriodicMessage.
2024-11-07 WIP: Refactor again, to use select_biased this time!
    Code size is about 1KB bigger than 8865002 (the one using &dyn).
    I think can shrink further once don't have to do generics for
    tx.transmit().
2024-11-07 WIP: Refactor PeriodicMessage to periodic_tick instead.
2024-11-07 fw: Small notes
2024-11-07 fw: Switch from lib+bin structure to single main.rs file.
    This allows simplifying the app task declarations to use 'extern "Rust"'.
2024-11-07 fw: Rename 'every' to 'repeater', add some sugar in on_next()
2024-11-07 fw: Refactor airbag_control to use PeriodicMessage
2024-11-07 WIP: fw: take a stab at making a PeriodicMessage trait, refactor IEB
2024-11-07 fw: can_queue: Make a note about use of static.
2024-11-07 fw: Swap airbag task back to the old simpler method.
    It doesn't do too much, and this is both easier to read and less code.
2024-11-07 fw: Use tick count for log timestamps.
2024-11-08 fw: Fix bugs causing panics in the repeater code.
    Can go to Ready with no unexpected DTCs showing!
2024-11-09 fw: Remove debugging the Format output of Messages, it's too slow.
2024-11-09 fw: Reset the SCU state while the vehicle is off.
2024-11-09 fw: Add code to emulate SCU PWM RX and TX, plus CAN actuator request
2024-11-09 fw: shift_control: When duty changes, it changes from a falling edge.
2024-11-09 fw: shift_control: Working SCU emulation
    - Pulled fault codes, everything seems happy
    - Tested the PWM TX on the scope for Neutral and Park
    - Tested the PWM RX by disabling listening for the CAN request
    and verified it was received OK.
    - Was able to go to Drive and apply torque to the motor (because
    the real parking actuator is still locked)
2024-11-17 fw: Break out the charge port locked to a variable.
    This is just so that I could do some quick hacky tests where I hard-coded
    it always show locked.
    This version of the firmware has gone into Drive, applied motor torque, and
    charged from an EVSE (with Ignition On, the IG3-only version needs a bit of
    thinking through.)
2024-12-07 fw: Add (untested) charge port lock actuator driver.
2024-12-07 fw: Split Fresh into a struct and a trait, make stale time a const generic.
2024-12-07 fw: Working charge port lock/unlock
    Simplified the logic as it seems the OBC has its own timeout
    for when the actuator fails to operate as expected.
2024-12-08 fw: Add dedicated tracking of ignition state, WIP for standby.
    Currently the MCU doesn't go to standby, but the rest seems to work
    as designed.
2024-12-18 fw: Working standby mode when idle.
    *Flips "days since didn't enable clock to STM peripheral" sign
    back to zero.*
    No wakeup, as the hw-dev board isn't set up properly for wakeup
    signals.
2024-12-22 Add top-level README, licenses, license info.
    This includes deleting the licenses and README from the firmware that came
    in from https://github.com/rtic-rs/defmt-app-template - However I think
    almost all of the code from that original template has been totally
    replaced with new work, apart from the .cargo/config.toml and maybe some of
    the Cargo.toml boilerplate.
